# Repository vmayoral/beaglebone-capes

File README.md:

My collection of BB and BBB capes.

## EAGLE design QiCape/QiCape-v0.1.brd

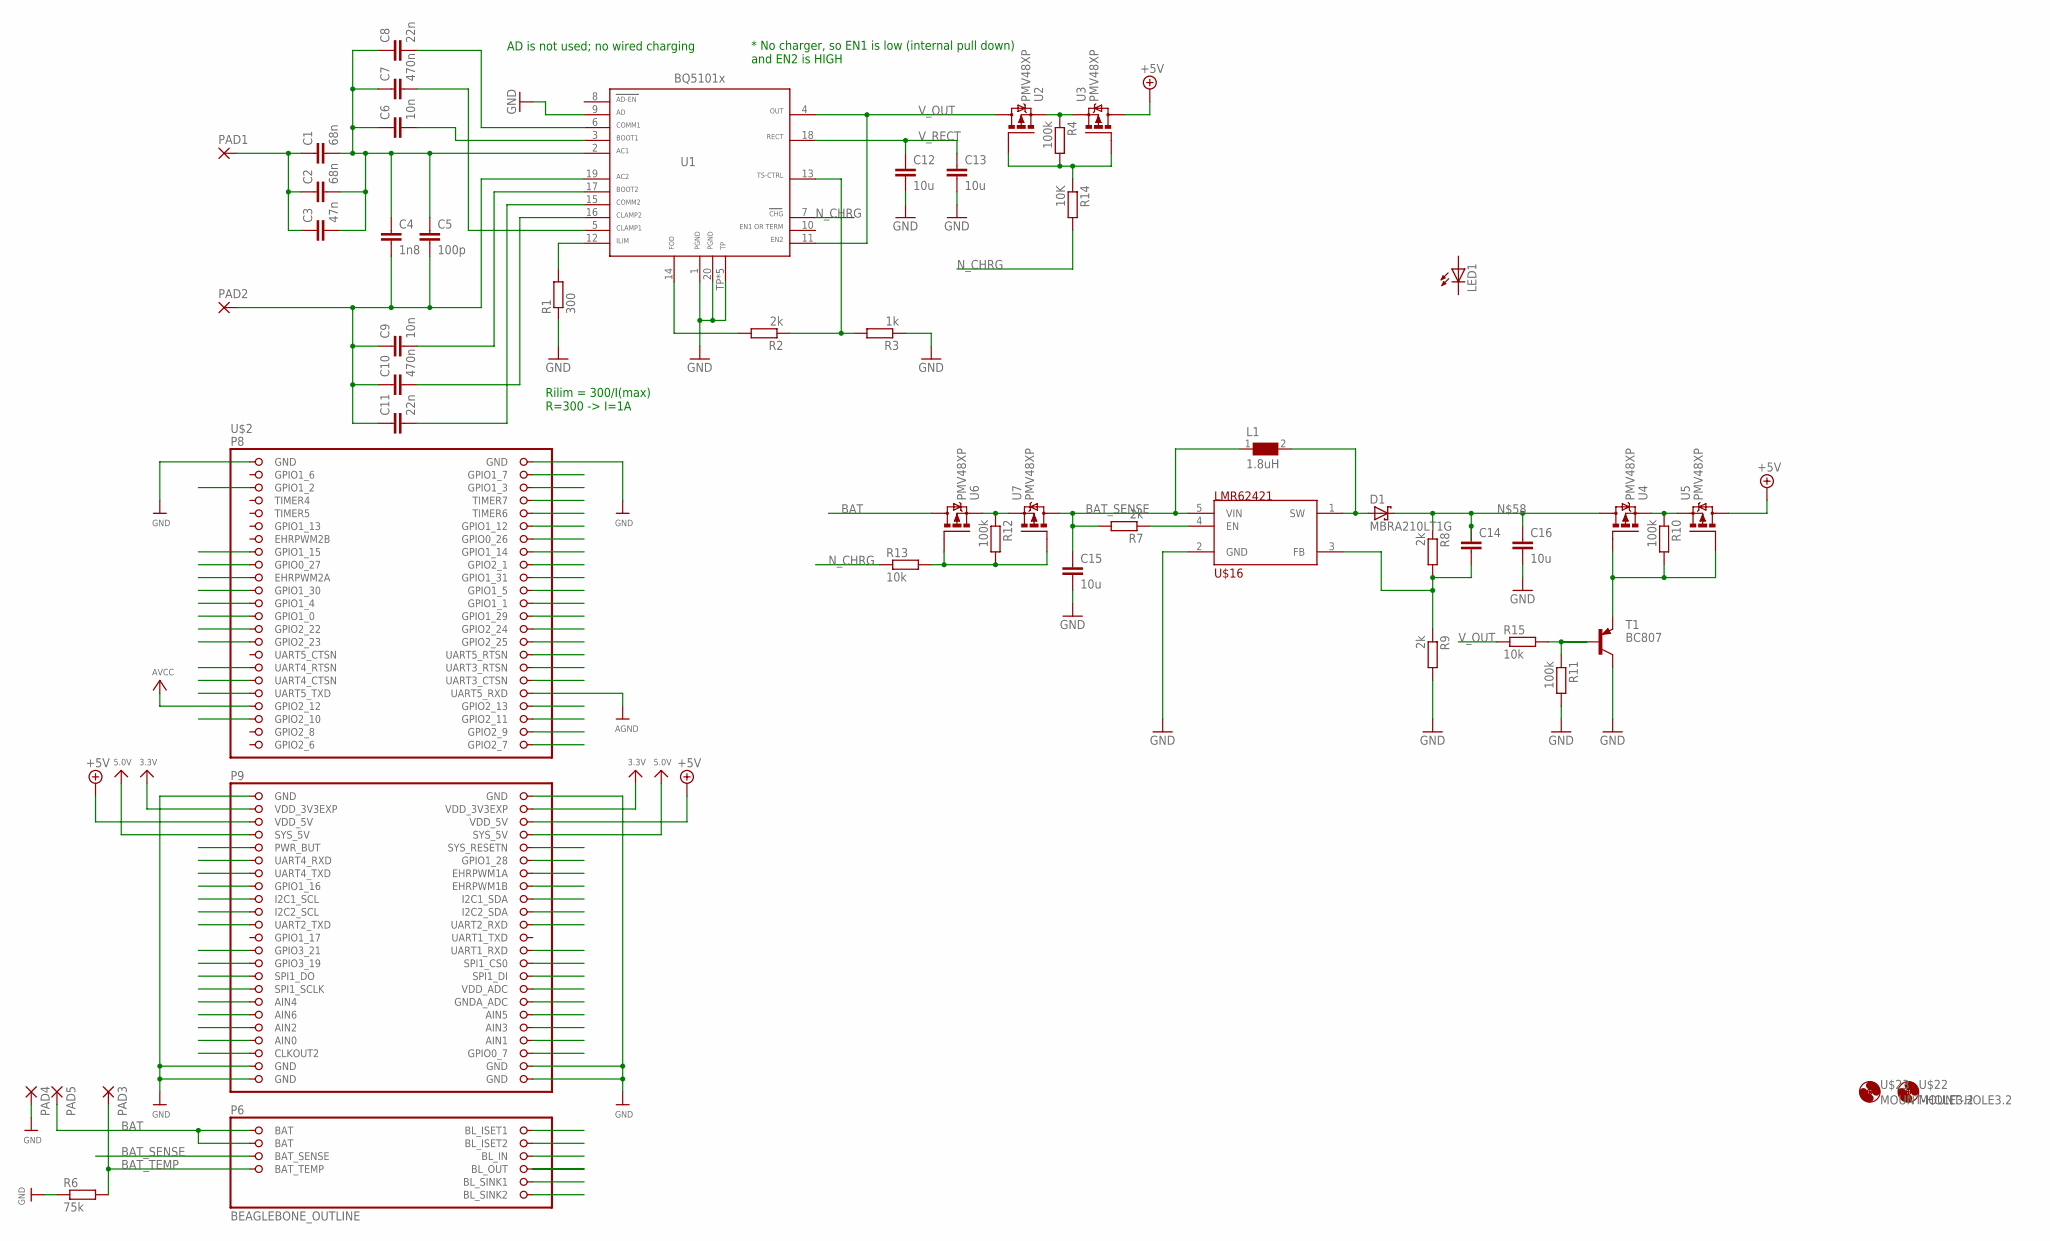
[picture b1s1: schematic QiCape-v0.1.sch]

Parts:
C1, C2: 68n; C0603K; MPN C0603C682K5RACTU
C3: 47n; C0603K; MPN C0603C473K5RACTU
C4: 1n8; C0603K; MPN C0603C182K5RACTU
C5: 100p; C0603K; MPN C0603C101K5RACTU
C6, C9: 10n; C0603K
C7, C10: 470n; C0603K
C8, C11: 22n; C0603K; MPN C0603C223K5RACTU
C12, C13, C15: 10u; C0805; MPN GRM21BR61E106KA73L
C14: C-EUC0402; C0402
C16: 10u; C1206; MPN C3216X5R0J106K
D1: MBRA210LT1G; SMA-DO214AC
L1: 1.8uH; WE-TPC_5818/5828; MPN 7440520018
LED1: LEDCHIP-LED0603; CHIP-LED0603
PAD1, PAD2, PAD3, PAD4, PAD5: 1,6/0,8
R1: 300; R0402; MPN ERJ3EKF3000V
R2, R7, R8, R9: 2k; R0402; MPN ERJ3EKF3000V
R3: 1k; R0402; MPN ERJ3EKF3000V
R4, R10, R11, R12: 100k; R0402; MPN ERJ3EKF3000V
R6: 75k; R0402; MPN ERJ3EKF3000V
R13, R15: 10k; R0402; MPN ERJ3EKF3000V
R14: 10K; R0402; MPN ERJ3EKF3000V
T1: BC807; SOT23-BEC
U1: BQ51013ARHL20; RHL; MPN BQ51013ARHLT
U2, U3, U4, U5, U6, U7: PMV48XP; SOT95P230X110-3N
U$2: BEAGLEBONE_OUTLINE; BEAGLEBONE_SHIELD_VS
U$16: LMR62421; SOT23-5
U$22, U$23: MOUNT-HOLE3.2; 3,2

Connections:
3.3V: U$2.49 (VDD_3V3EXP), U$2.50 (VDD_3V3EXP)
5.0V: U$2.53 (SYS_5V), U$2.54 (SYS_5V)
+5V: U3.3 (D), U5.3 (D), U$2.51 (VDD_5V), U$2.52 (VDD_5V)
AGND: U$2.38 (UART5_RXD)
AVCC: U$2.39 (GPIO2_12)
BAT: PAD5.1, U6.3 (D), U$2.1_BAT (BAT), U$2.2_BAT (BAT)
BAT_SENSE: C15.1, L1.1, R7.2, U7.3 (D), U$2.3_BAT_SENSE (BAT_SENSE), U$16.5 (VIN)
BAT_TEMP: PAD3.1, R6.2, U$2.4_BAT_TEMP (BAT_TEMP)
BL_IN: U$2.8_BL_IN (BL_IN)
BL_OUT: U$2.7_BL_OUT (BL_OUT)
GND: C12.2, C13.2, C15.2, C16.2, PAD4.1, R1.1, R3.1, R6.1, R9.2, R11.2, T1.C, U1.1, U1.9, U1.20, U1.TP, U1.TP1 (TP), U1.TP2 (TP), U1.TP3 (TP), U1.TP4 (TP), U$2.1 (GND), U$2.2 (GND), U$2.47 (GND), U$2.48 (GND), U$2.89 (GND), U$2.90 (GND), U$2.91 (GND), U$2.92 (GND), U$16.2 (GND)
GPIO1_6: U$2.3 (GPIO1_6)
GPIO2_6: U$2.45 (GPIO2_6)
GPIO2_8: U$2.43 (GPIO2_8)
unnamed: R4.1, U2.2 (S), U3.2 (S)
unnamed: C1.2, C2.2, C3.2, C4.1, C5.1, C6.1, C7.1, C8.1, U1.2
unnamed: C6.2, U1.3
unnamed: C7.2, U1.5
unnamed: C8.2, U1.6
unnamed: C1.1, C2.1, C3.1, PAD1.1
unnamed: C4.2, C5.2, C9.1, C10.1, C11.1, PAD2.1, U1.19
unnamed: C9.2, U1.17
unnamed: C11.2, U1.15
unnamed: C10.2, U1.16
unnamed: R1.2, U1.12
unnamed: R10.2, T1.E, U4.1 (G), U5.1 (G)
unnamed: R2.2, U1.14
unnamed: R2.1, R3.2, U1.13
unnamed: C14.2, R8.2, R9.1, U$16.3 (FB)
unnamed: R11.1, R15.2, T1.B
unnamed: C14.1, C16.1, D1.K (C), R8.1, U4.3 (D)
unnamed: R7.1, U$16.4 (EN)
unnamed: R10.1, U4.2 (S), U5.2 (S)
unnamed: R12.1, U6.2 (S), U7.2 (S)
unnamed: R4.2, R14.1, U2.1 (G), U3.1 (G)
unnamed: D1.A, L1.2, U$16.1 (SW)
N_CHRG: R13.1, R14.2, U1.7
N_CHRG1: R12.2, R13.2, U6.1 (G), U7.1 (G)
V_OUT: R15.1, U1.4, U1.11, U2.3 (D)
V_RECT: C12.1, C13.1, U1.18

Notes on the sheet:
AD is not used; no wired charging
Rilim = 300/I(max) R=300 -> I=1A
* No charger, so EN1 is low (internal pull down) and EN2 is HIGH

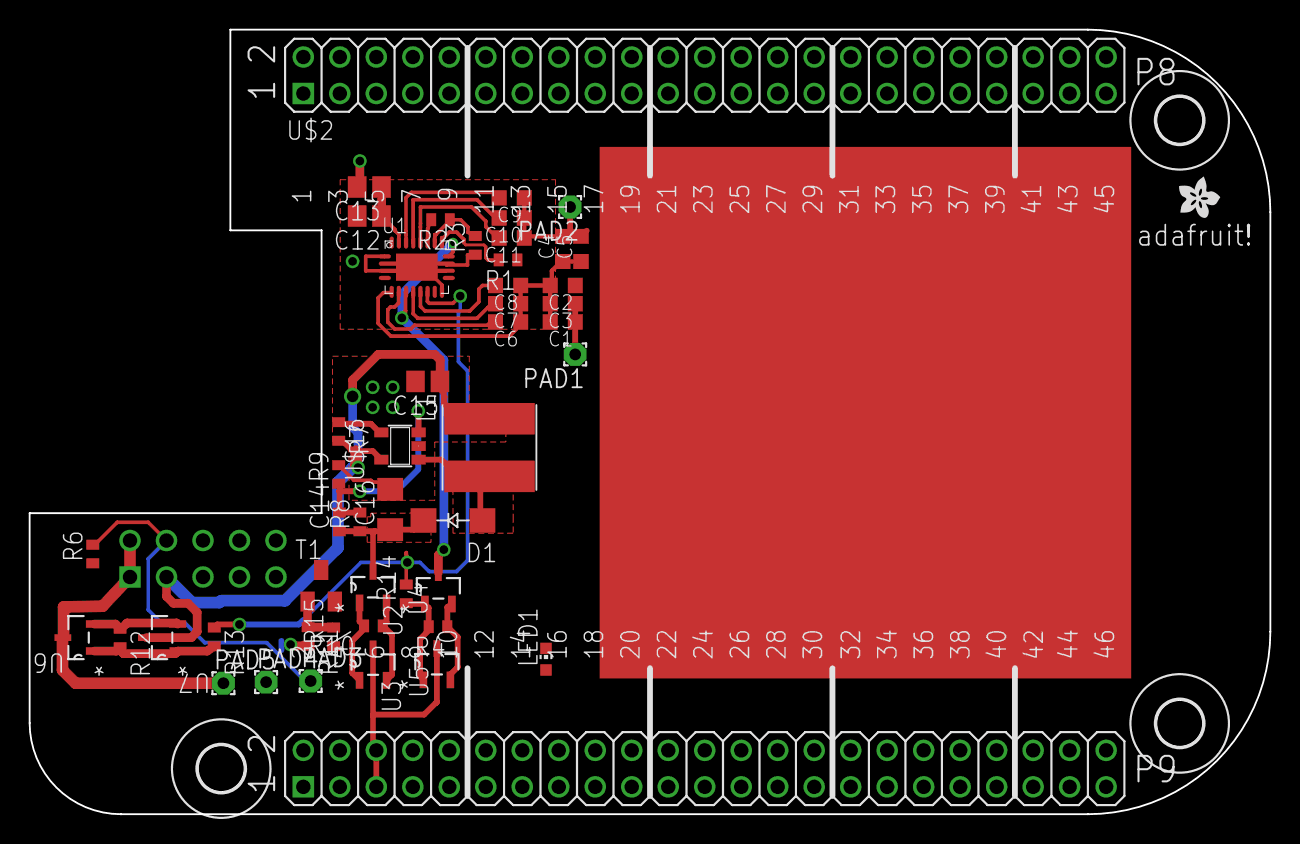
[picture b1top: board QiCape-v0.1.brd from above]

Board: 2 copper layers, 86.4 x 54.6 mm, 52 parts (0 on the bottom side), 33 nets.

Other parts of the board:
U$7: ADAFRUIT200MIL
U$17: 3,2

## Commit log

2013-12-11 QiCape added.
    Credit to "vsluiter" at Element14 forums.
2013-12-11 Added QiLiCape: A Qi standart cape for the BB.
    Credit to Dan Teodorescu <dan@ioclk.com>.

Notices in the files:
parts and their libraries:
EagleLibrary_Wuerth_Elektronik_eiSos_Ver: Copyright: Würth Elektronik
